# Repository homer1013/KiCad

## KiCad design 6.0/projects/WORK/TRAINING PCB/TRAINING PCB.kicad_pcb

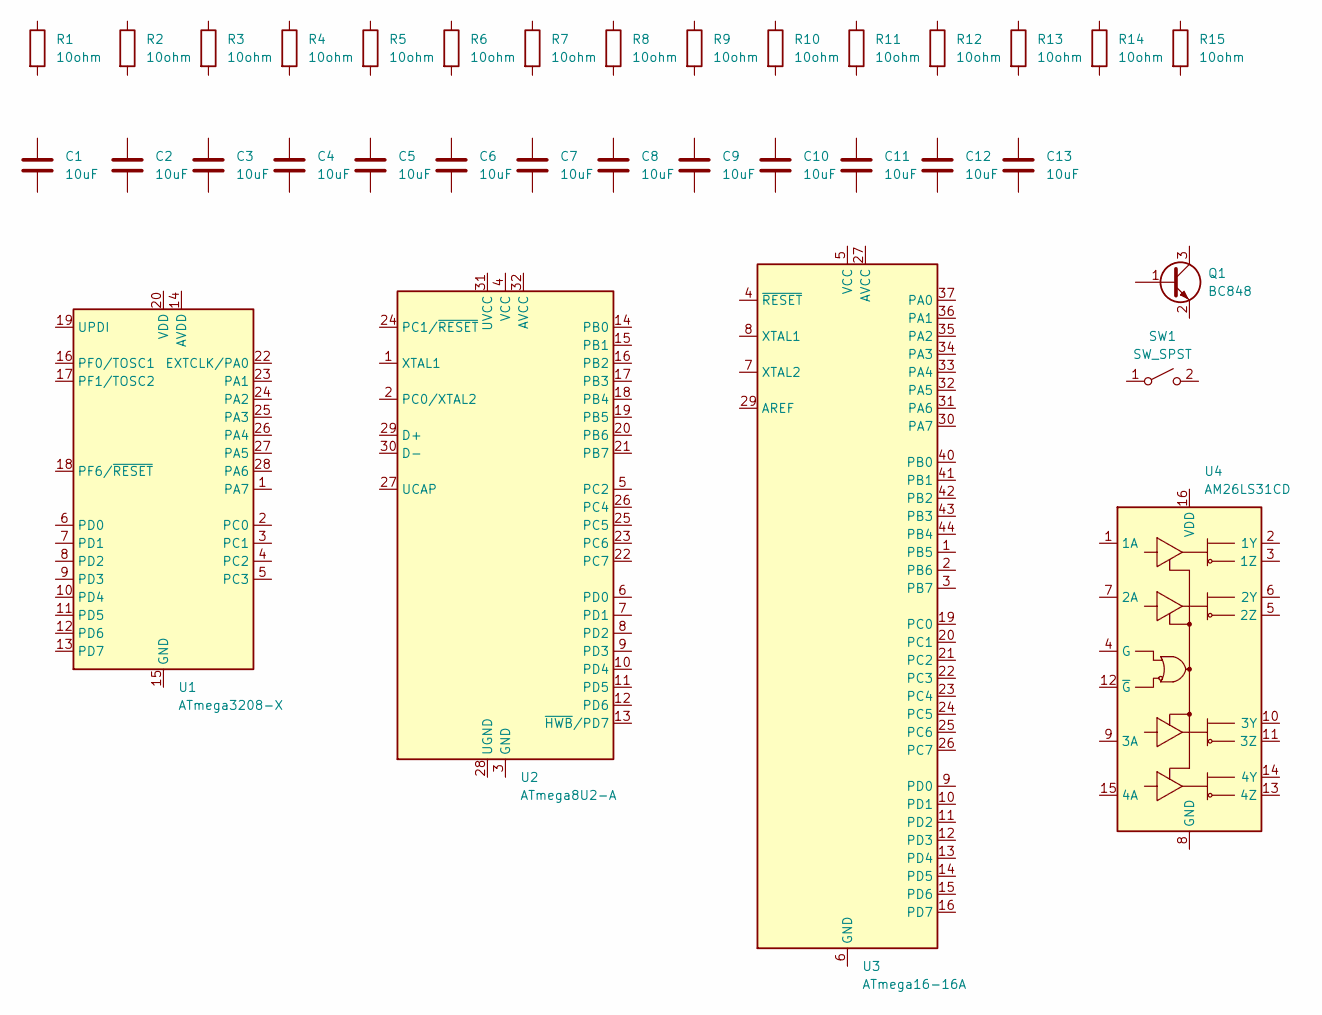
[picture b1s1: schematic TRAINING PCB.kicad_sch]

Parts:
C1: 10uF; C_0201_0603Metric
C2: 10uF; C_0402_1005Metric
C3: 10uF; C_0504_1310Metric
C4: 10uF; C_0603_1608Metric
C5: 10uF; C_0805_2012Metric
C6: 10uF; C_01005_0402Metric
C7: 10uF; C_1206_3216Metric
C8: 10uF; C_1210_3225Metric
C9: 10uF; C_1812_4532Metric
C10: 10uF; C_1825_4564Metric
C11: 10uF; C_2220_5650Metric
C12: 10uF; C_2225_5664Metric
C13: 10uF; C_3640_9110Metric
Q1: BC848; SOT-23
R1: 10ohm; R_0201_0603Metric
R2: 10ohm; R_0402_1005Metric
R3: 10ohm; R_0603_1608Metric
R4: 10ohm; R_0805_2012Metric
R5: 10ohm; R_0815_2038Metric
R6: 10ohm; R_01005_0402Metric
R7: 10ohm; R_1020_2550Metric
R8: 10ohm; R_1206_3216Metric
R9: 10ohm; R_1210_3225Metric
R10: 10ohm; R_1218_3246Metric
R11: 10ohm; R_1812_4532Metric
R12: 10ohm; R_2010_5025Metric
R13: 10ohm; R_2512_6332Metric
R14: 10ohm; R_2816_7142Metric
R15: 10ohm; R_4020_10251Metric
SW1: SW_SPST; SW_SPST_B3SL-1022P
U1: ATmega3208-X; SSOP-28_5.3x10.2mm_P0.65mm
U2: ATmega8U2-A; TQFP-32_7x7mm_P0.8mm
U3: ATmega16-16A; TQFP-44_10x10mm_P0.8mm
U4: AM26LS31CD; SOIC-16_3.9x9.9mm_P1.27mm

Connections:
unnamed: U1.15 (GND), U1.21 (GND)
unnamed: U3.5 (VCC), U3.17 (VCC), U3.38 (VCC)
unnamed: U3.6 (GND), U3.18 (GND), U3.28 (GND), U3.39 (GND)

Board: 2 copper layers, 34 parts (0 on the bottom side), 3 nets, no tracks yet.

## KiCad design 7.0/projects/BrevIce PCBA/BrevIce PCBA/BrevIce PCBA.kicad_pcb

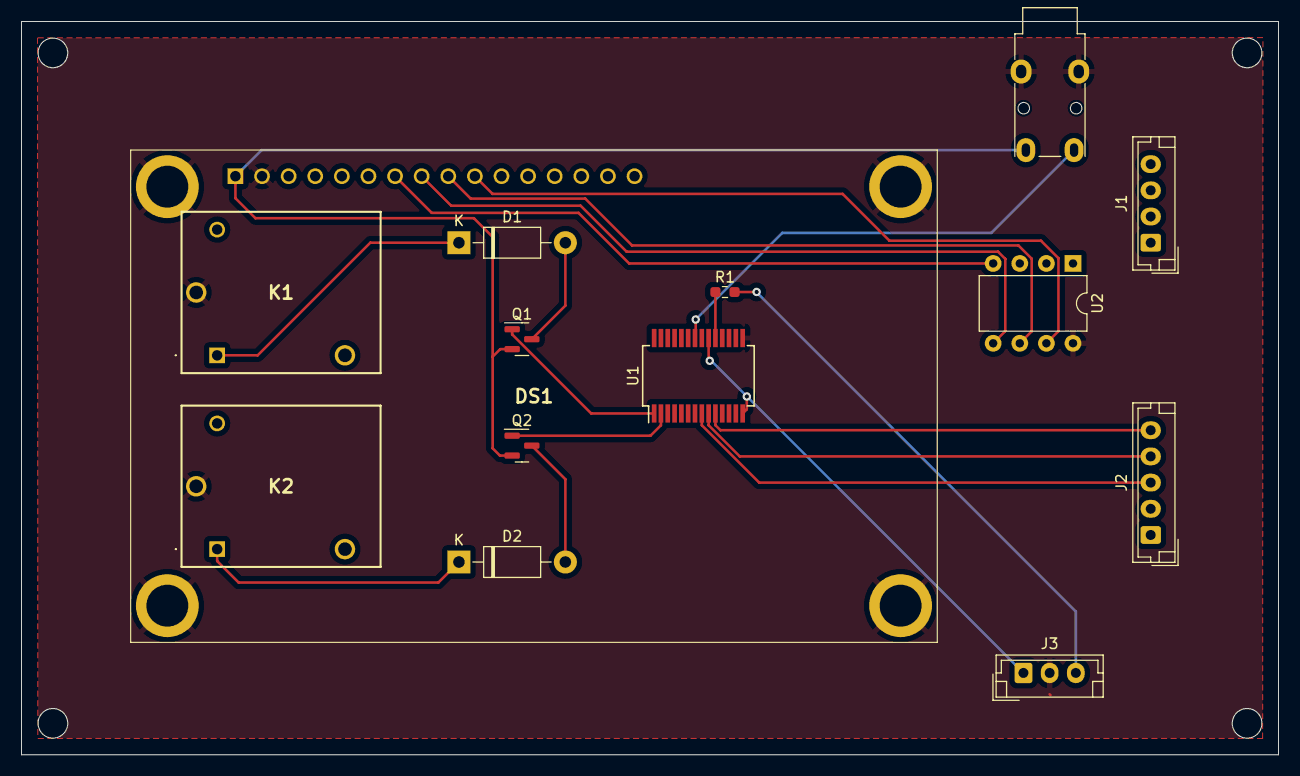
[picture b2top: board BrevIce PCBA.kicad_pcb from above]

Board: 2 copper layers, 120.0 x 70.0 mm, 14 parts (0 on the bottom side), 19 nets.

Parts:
D1, D2: 1N4001; D_DO-41_SOD81_P10.16mm_Horizontal
DS1: NHD-0420AZ-FL-YBW-33V3; NHD0420AZFLYBW33V3
J1: Conn_01x04_Socket; JST_EH_B4B-EH-A_1x04_P2.50mm_Vertical
J2: Conn_01x05_Socket; JST_EH_B5B-EH-A_1x05_P2.50mm_Vertical
J3: Conn_01x03_Socket; JST_EH_B3B-EH-A_1x03_P2.50mm_Vertical
J4: AudioPlug3; Jack_3.5mm_Lumberg_1503_07_Horizontal
K1, K2: AWHSH105D00G
Q1, Q2: AO3400A; SOT-23
R1: 4.7K; R_0603_1608Metric_Pad0.98x0.95mm_HandSolder
U1: ATmega3208-X; SSOP-28_5.3x10.2mm_P0.65mm
U2: PCF8574; DIP-8_W7.62mm

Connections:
+5V: DS1.1 (VSS), J4.S, Q1.2 (S), Q2.2 (S)
GND: DS1.2 (VDD), DS1.MH1, DS1.MH2, DS1.MH3, DS1.MH4, J3.2, J4.T, K1.4 (COM), K2.4 (COM), U1.15 (GND), U1.21 (GND), U2.8 (VSS)
unnamed: D1.2 (A), Q1.3 (D)
unnamed: D1.1 (K), K1.1 (COIL_1)
unnamed: D2.2 (A), Q2.3 (D)
unnamed: D2.1 (K), K2.1 (COIL_1)
unnamed: DS1.7 (DB0), U2.4 (P0)
unnamed: DS1.8 (DB1), U2.5 (P1)
unnamed: DS1.9 (DB2), U2.6 (P2)
unnamed: DS1.10 (DB3), U2.7 (P3)
unnamed: J2.3, U1.8 (PD2)
unnamed: J2.4, U1.9 (PD3)
unnamed: J2.5, U1.10 (PD4)
unnamed: J3.1, U1.14 (AVDD), U1.20 (VDD)
unnamed: J3.3, R1.2
unnamed: Q1.1 (G), U1.1 (PA7)
unnamed: Q2.1 (G), U1.2 (PC0)
unnamed: J4.R, U1.22 (EXTCLK/PA0)
unnamed: R1.1, U1.19 (UPDI)

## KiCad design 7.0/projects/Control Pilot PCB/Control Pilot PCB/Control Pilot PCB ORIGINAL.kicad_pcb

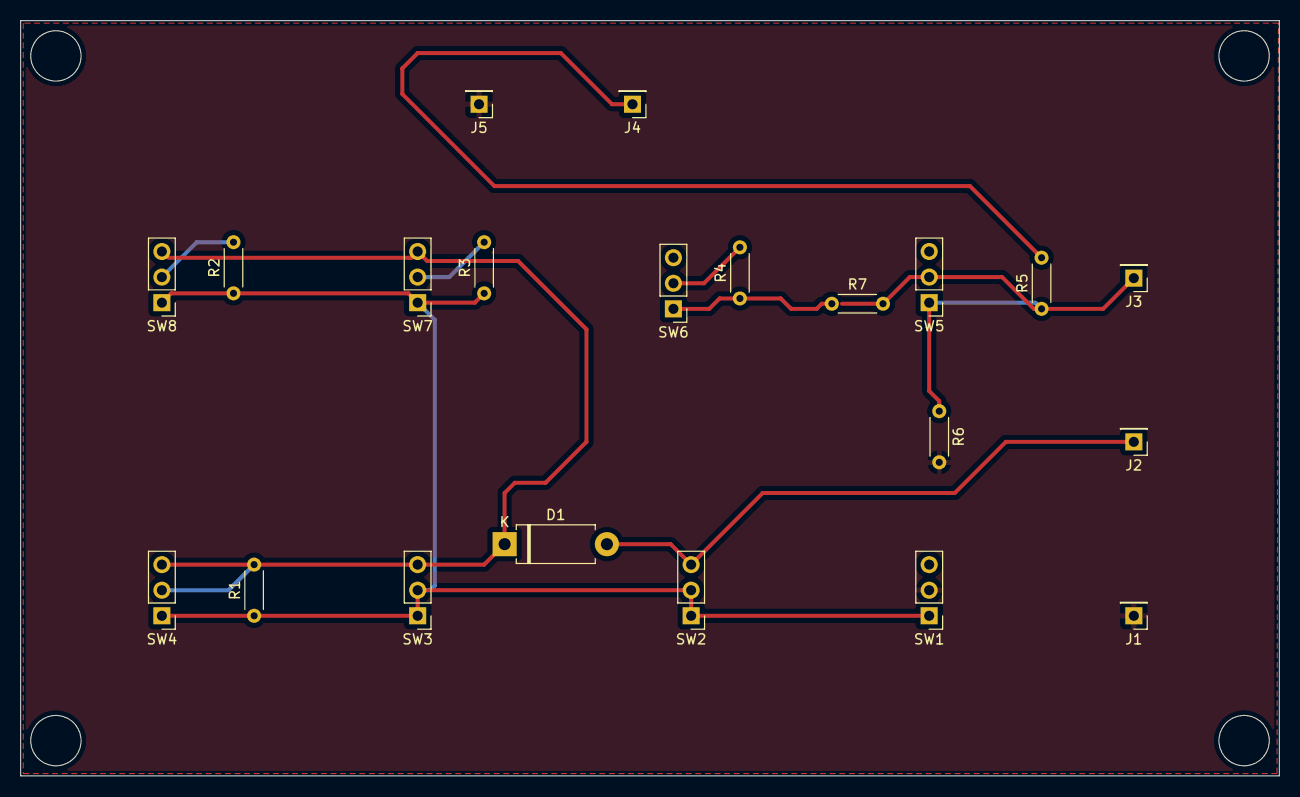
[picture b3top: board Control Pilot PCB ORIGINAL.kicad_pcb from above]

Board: 2 copper layers, 125.0 x 75.0 mm, 21 parts (0 on the bottom side), 11 nets.

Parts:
D1: D; D_DO-15_P10.16mm_Horizontal
J1, J2, J3, J4, J5: Conn_01x01; PinHeader_1x01_P2.54mm_Vertical
R1: 2.74K; R_Axial_DIN0204_L3.6mm_D1.6mm_P5.08mm_Horizontal
R2: 1.3K; R_Axial_DIN0204_L3.6mm_D1.6mm_P5.08mm_Horizontal
R3: 270; R_Axial_DIN0204_L3.6mm_D1.6mm_P5.08mm_Horizontal
R4, R5: 330; R_Axial_DIN0204_L3.6mm_D1.6mm_P5.08mm_Horizontal
R6: 2.7K; R_Axial_DIN0204_L3.6mm_D1.6mm_P5.08mm_Horizontal
R7: 150; R_Axial_DIN0204_L3.6mm_D1.6mm_P5.08mm_Horizontal
SW1, SW2, SW3, SW4, SW5, SW6, SW7, SW8: SW_SPDT; PinHeader_1x03_P2.54mm_Vertical

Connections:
+5V: J4.1, R5.2
Earth_Protective: J1.1, J5.1, R6.2, SW1.2 (B)
unnamed: D1.2 (A), J2.1, SW2.3 (C)
unnamed: D1.1 (K), R1.2, SW3.3 (C), SW4.2 (B), SW4.3 (C), SW7.3 (C), SW8.3 (C)
unnamed: J3.1, R7.2, SW5.2 (B)
unnamed: R1.1, R2.1, R3.1, SW1.1 (A), SW2.1 (A), SW2.2 (B), SW3.1 (A), SW3.2 (B), SW4.1 (A), SW7.1 (A), SW8.1 (A)
unnamed: R5.1, R6.1, SW5.1 (A)
unnamed: R4.1, R7.1, SW6.1 (A)
unnamed: R4.2, SW6.2 (B)
unnamed: R3.2, SW7.2 (B)
unnamed: R2.2, SW8.2 (B)

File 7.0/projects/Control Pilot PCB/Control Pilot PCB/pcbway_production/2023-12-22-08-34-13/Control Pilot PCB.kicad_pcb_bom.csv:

designator,quantity,value,pack,mpn,mount_type
D1,1,D,D_DO-15_P10.16mm_Horizontal,,tht
"J1, J2, J3, J4, J5",5,Conn_01x01,PinHeader_1x01_P2.54mm_Vertical,,tht
R1,1,2.74K,R_Axial_DIN0204_L3.6mm_D1.6mm_P5.08mm_Horizontal,,tht
R2,1,1.3K,R_Axial_DIN0204_L3.6mm_D1.6mm_P5.08mm_Horizontal,,tht
R3,1,270,R_Axial_DIN0204_L3.6mm_D1.6mm_P5.08mm_Horizontal,,tht
"R4, R5",2,330,R_Axial_DIN0204_L3.6mm_D1.6mm_P5.08mm_Horizontal,,tht
R6,1,2.7K,R_Axial_DIN0204_L3.6mm_D1.6mm_P5.08mm_Horizontal,,tht
R7,1,150,R_Axial_DIN0204_L3.6mm_D1.6mm_P5.08mm_Horizontal,,tht
"SW1, SW2, SW3, SW4, SW5, SW6, SW7, SW8",8,SW_SPDT,PinHeader_1x03_P2.54mm_Vertical,,tht

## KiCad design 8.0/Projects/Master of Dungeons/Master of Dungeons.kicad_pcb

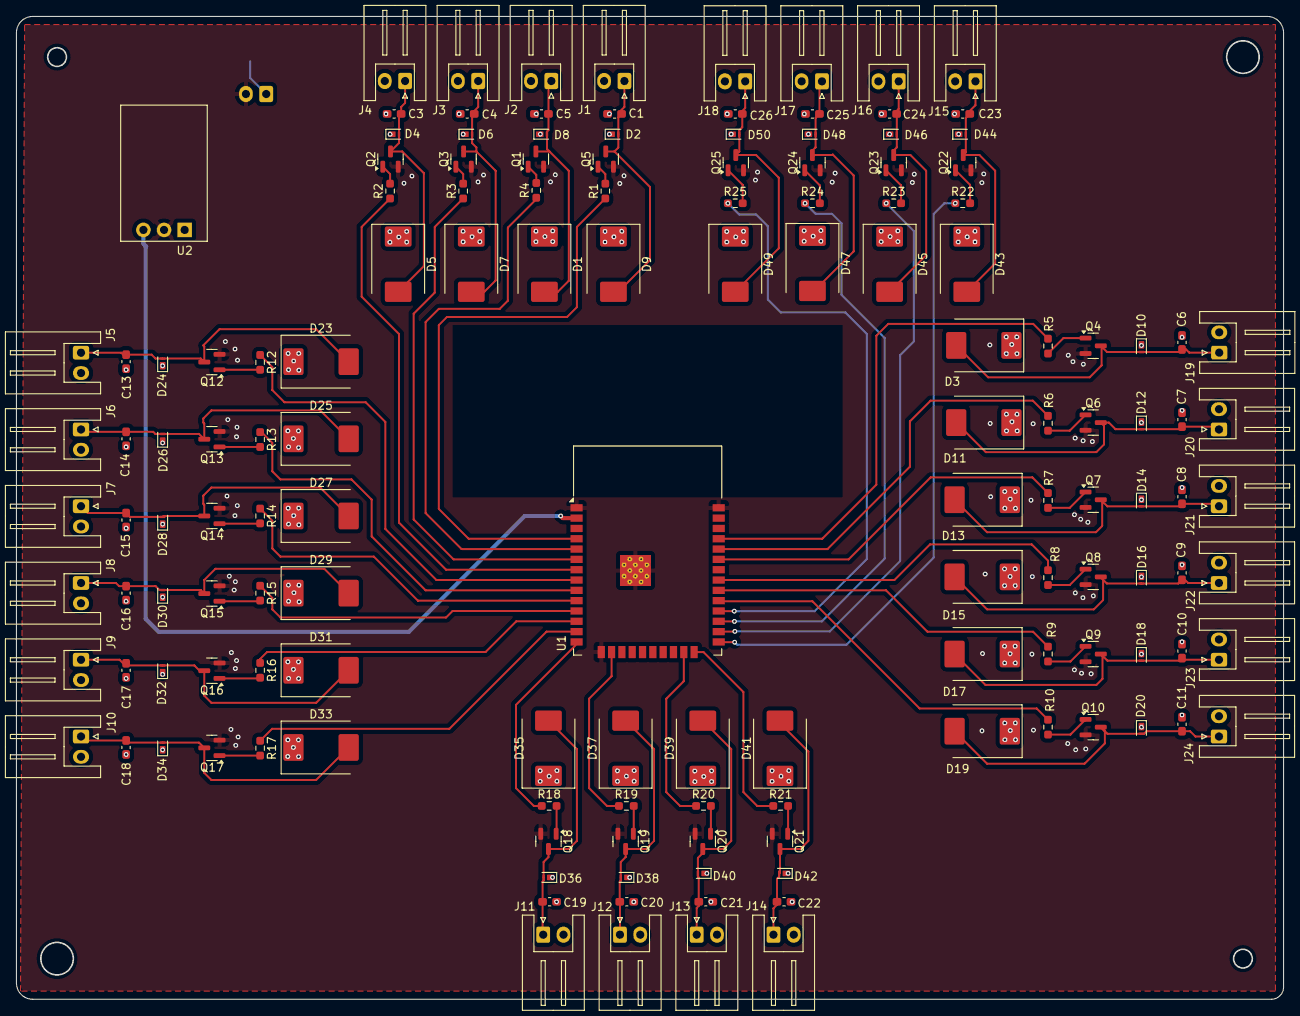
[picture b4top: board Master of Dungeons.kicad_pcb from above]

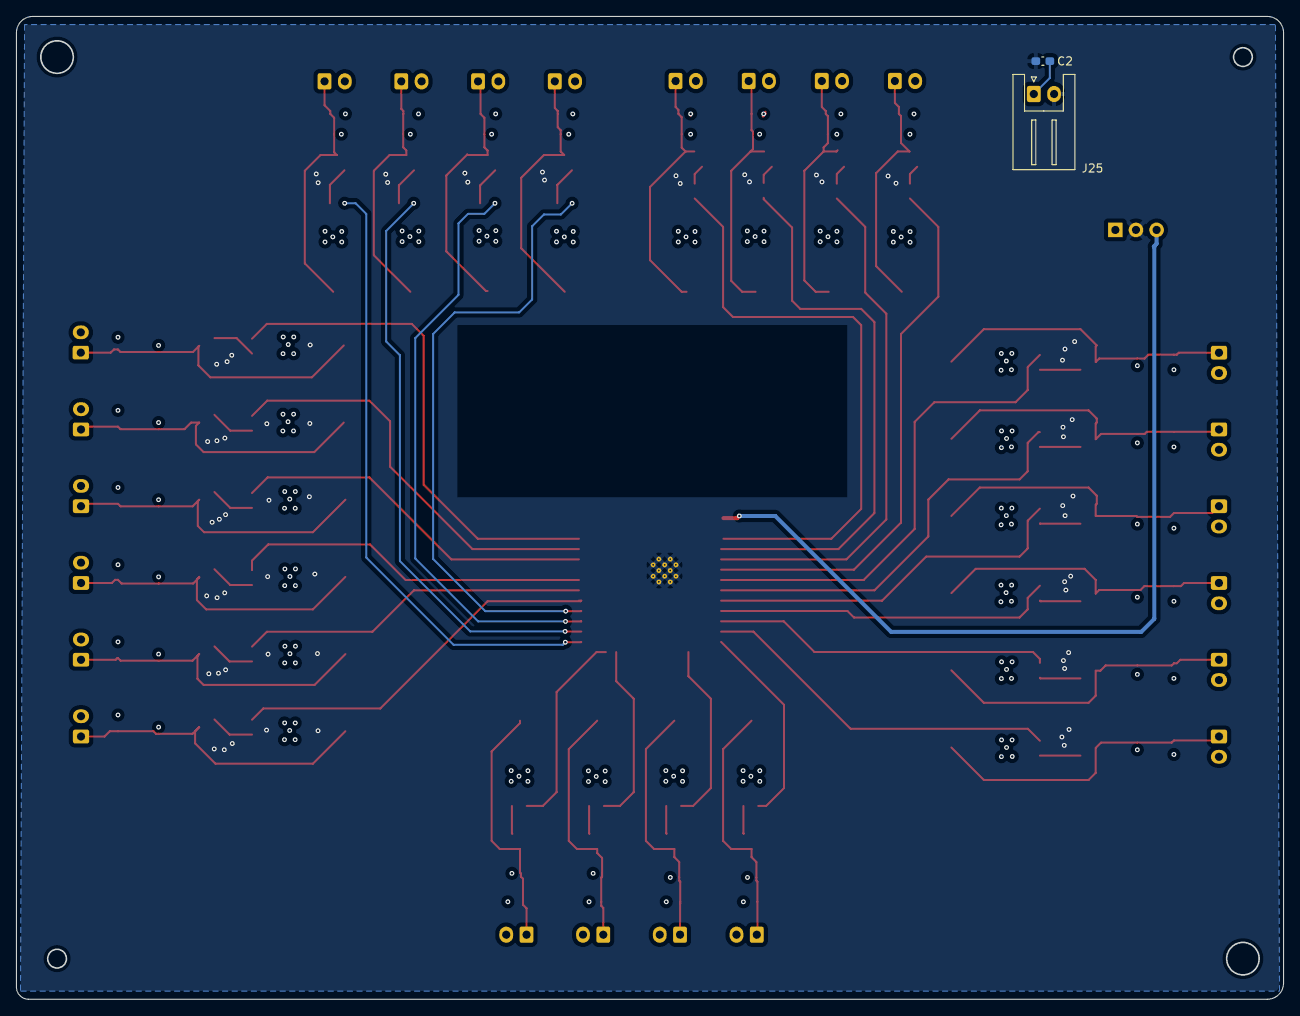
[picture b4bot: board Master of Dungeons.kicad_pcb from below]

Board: 4 copper layers, 156.0 x 121.0 mm, 148 parts (2 on the bottom side), 75 nets.

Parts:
C1, C2, C3, C4, C5, C6, C7, C8, C9, C10, C11, C13, C14, C15, C16, C17, C18, C19, C20, C21, C22, C23, C24, C25, C26: 100nF; C_0603_1608Metric_Pad1.08x0.95mm_HandSolder
D1, D3, D5, D7, D9, D11, D13, D15, D17, D19, D23, D25, D27, D29, D31, D33, D35, D37, D39, D41, D43, D45, D47, D49: B340; D_SMC
D2, D4, D6, D8, D10, D12, D14, D16, D18, D20, D24, D26, D28, D30, D32, D34, D36, D38, D40, D42, D44, D46, D48, D50: PTVS12VZ1USK; Nexperia_DSN1608-2_1.6x0.8mm
J1: sensPin1; JST_XH_S2B-XH-A_1x02_P2.50mm_Horizontal
J2: sensPin2; JST_XH_S2B-XH-A_1x02_P2.50mm_Horizontal
J3: sensPin3; JST_XH_S2B-XH-A_1x02_P2.50mm_Horizontal
J4: sensPin4; JST_XH_S2B-XH-A_1x02_P2.50mm_Horizontal
J5: togglePin1; JST_XH_S2B-XH-A_1x02_P2.50mm_Horizontal
J6: togglePin2; JST_XH_S2B-XH-A_1x02_P2.50mm_Horizontal
J7: togglePin3; JST_XH_S2B-XH-A_1x02_P2.50mm_Horizontal
J8: togglePin4; JST_XH_S2B-XH-A_1x02_P2.50mm_Horizontal
J9: togglePin5; JST_XH_S2B-XH-A_1x02_P2.50mm_Horizontal
J10: togglePin6; JST_XH_S2B-XH-A_1x02_P2.50mm_Horizontal
J11: dimPin1; JST_XH_S2B-XH-A_1x02_P2.50mm_Horizontal
J12: dimPin2; JST_XH_S2B-XH-A_1x02_P2.50mm_Horizontal
J13: dimPin3; JST_XH_S2B-XH-A_1x02_P2.50mm_Horizontal
J14: dimPin4; JST_XH_S2B-XH-A_1x02_P2.50mm_Horizontal
J15: timerPin1; JST_XH_S2B-XH-A_1x02_P2.50mm_Horizontal
J16: timerPin2; JST_XH_S2B-XH-A_1x02_P2.50mm_Horizontal
J17: timerPin3; JST_XH_S2B-XH-A_1x02_P2.50mm_Horizontal
J18: timerPin4; JST_XH_S2B-XH-A_1x02_P2.50mm_Horizontal
J19: sequencePin1; JST_XH_S2B-XH-A_1x02_P2.50mm_Horizontal
J20: sequencePin2; JST_XH_S2B-XH-A_1x02_P2.50mm_Horizontal
J21: sequencePin3; JST_XH_S2B-XH-A_1x02_P2.50mm_Horizontal
J22: sequencePin4; JST_XH_S2B-XH-A_1x02_P2.50mm_Horizontal
J23: sequencePin5; JST_XH_S2B-XH-A_1x02_P2.50mm_Horizontal
J24: sequencePin6; JST_XH_S2B-XH-A_1x02_P2.50mm_Horizontal
J25: 5VDC; JST_XH_S2B-XH-A_1x02_P2.50mm_Horizontal
Q1, Q2, Q3, Q4, Q5, Q6, Q7, Q8, Q9, Q10, Q12, Q13, Q14, Q15, Q16, Q17, Q18, Q19, Q20, Q21, Q22, Q23, Q24, Q25: IRLML6244; SOT-23
R1, R2, R3, R4, R5, R6, R7, R8, R9, R10, R12, R13, R14, R15, R16, R17, R18, R19, R20, R21, R22, R23, R24, R25: 100ohm; R_0603_1608Metric_Pad0.98x0.95mm_HandSolder
U1: ESP32-WROOM-32D
U2: OKI-78SR-3.3_1.5-W36H-C; Converter_DCDC_Murata_OKI-78SR_Horizontal

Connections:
+5V: C1.1, C3.1, C4.1, C5.1, C6.1, C7.1, C8.1, C9.1, C10.1, C11.1, C13.1, C14.1, C15.1, C16.1, C17.1, C18.1, C19.1, C20.1, C21.1, C22.1, C23.1, C24.1, C25.1, C26.1, D1.1 (K), D2.1 (K), D3.1 (K), D4.1 (K), D5.1 (K), D6.1 (K), D7.1 (K), D8.1 (K), D9.1 (K), D10.1 (K), D11.1 (K), D12.1 (K), D13.1 (K), D14.1 (K), D15.1 (K), D16.1 (K), D17.1 (K), D18.1 (K), D19.1 (K), D20.1 (K), D23.1 (K), D24.1 (K), D25.1 (K), D26.1 (K), D27.1 (K), D28.1 (K), D29.1 (K), D30.1 (K), D31.1 (K), D32.1 (K), D33.1 (K), D34.1 (K), D35.1 (K), D36.1 (K), D37.1 (K), D38.1 (K), D39.1 (K), D40.1 (K), D41.1 (K), D42.1 (K), D43.1 (K), D44.1 (K), D45.1 (K), D46.1 (K), D47.1 (K), D48.1 (K), D49.1 (K), D50.1 (K), J1.2, J2.2, J3.2, J4.2, J5.2, J6.2, J7.2, J8.2, J9.2, J10.2, J11.2, J12.2, J13.2, J14.2, J15.2, J16.2, J17.2, J18.2, J19.2, J20.2, J21.2, J22.2, J23.2, J24.2, J25.1, U2.1 (IN)
DIM1: R18.1, U1.14 (IO12)
DIM2: R19.1, U1.16 (IO13)
DIM3: R20.1, U1.23 (IO15)
DIM4: R21.1, U1.24 (IO2)
GND: C2.1, J25.2, Q1.2 (S), Q2.2 (S), Q3.2 (S), Q4.2 (S), Q5.2 (S), Q6.2 (S), Q7.2 (S), Q8.2 (S), Q9.2 (S), Q10.2 (S), Q12.2 (S), Q13.2 (S), Q14.2 (S), Q15.2 (S), Q16.2 (S), Q17.2 (S), Q18.2 (S), Q19.2 (S), Q20.2 (S), Q21.2 (S), Q22.2 (S), Q23.2 (S), Q24.2 (S), Q25.2 (S), U1.1 (GND), U1.15 (GND), U1.38 (GND), U1.39 (GND), U2.2 (GND)
unnamed: C5.2, D1.2 (A), D8.2 (A), J2.1, Q1.3 (D)
unnamed: C1.2, D2.2 (A), D9.2 (A), J1.1, Q5.3 (D)
unnamed: C3.2, D4.2 (A), D5.2 (A), J4.1, Q2.3 (D)
unnamed: C4.2, D6.2 (A), D7.2 (A), J3.1, Q3.3 (D)
unnamed: C6.2, D3.2 (A), D10.2 (A), J19.1, Q4.3 (D)
unnamed: C7.2, D11.2 (A), D12.2 (A), J20.1, Q6.3 (D)
unnamed: C8.2, D13.2 (A), D14.2 (A), J21.1, Q7.3 (D)
unnamed: C9.2, D15.2 (A), D16.2 (A), J22.1, Q8.3 (D)
unnamed: C10.2, D17.2 (A), D18.2 (A), J23.1, Q9.3 (D)
unnamed: C11.2, D19.2 (A), D20.2 (A), J24.1, Q10.3 (D)
unnamed: C13.2, D23.2 (A), D24.2 (A), J5.1, Q12.3 (D)
unnamed: C14.2, D25.2 (A), D26.2 (A), J6.1, Q13.3 (D)
unnamed: C15.2, D27.2 (A), D28.2 (A), J7.1, Q14.3 (D)
unnamed: C16.2, D29.2 (A), D30.2 (A), J8.1, Q15.3 (D)
unnamed: C17.2, D31.2 (A), D32.2 (A), J9.1, Q16.3 (D)
unnamed: C18.2, D33.2 (A), D34.2 (A), J10.1, Q17.3 (D)
unnamed: C19.2, D35.2 (A), D36.2 (A), J11.1, Q18.3 (D)
unnamed: C20.2, D37.2 (A), D38.2 (A), J12.1, Q19.3 (D)
unnamed: C21.2, D39.2 (A), D40.2 (A), J13.1, Q20.3 (D)
unnamed: C22.2, D41.2 (A), D42.2 (A), J14.1, Q21.3 (D)
unnamed: C23.2, D43.2 (A), D44.2 (A), J15.1, Q22.3 (D)
unnamed: C24.2, D45.2 (A), D46.2 (A), J16.1, Q23.3 (D)
unnamed: C25.2, D47.2 (A), D48.2 (A), J17.1, Q24.3 (D)
unnamed: C26.2, D49.2 (A), D50.2 (A), J18.1, Q25.3 (D)
unnamed: Q1.1 (G), R4.2
unnamed: Q2.1 (G), R2.2
unnamed: Q3.1 (G), R3.2
unnamed: Q4.1 (G), R5.2
unnamed: Q5.1 (G), R1.2
unnamed: Q6.1 (G), R6.2
unnamed: Q7.1 (G), R7.2
unnamed: Q8.1 (G), R8.2
unnamed: Q9.1 (G), R9.2
unnamed: Q10.1 (G), R10.2
unnamed: Q12.1 (G), R12.2
unnamed: Q13.1 (G), R13.2
unnamed: Q14.1 (G), R14.2
unnamed: Q15.1 (G), R15.2
unnamed: Q16.1 (G), R16.2
unnamed: Q17.1 (G), R17.2
unnamed: Q18.1 (G), R18.2
unnamed: Q19.1 (G), R19.2
unnamed: Q20.1 (G), R20.2
unnamed: Q21.1 (G), R21.2
unnamed: Q22.1 (G), R22.2
unnamed: Q23.1 (G), R23.2
unnamed: Q24.1 (G), R24.2
unnamed: Q25.1 (G), R25.2
unnamed: R3.1, U1.6 (IO34)
unnamed: R2.1, U1.7 (IO35)
unnamed: R4.1, U1.5 (SENSOR_VN)
unnamed: R1.1, U1.4 (SENSOR_VP)
unnamed: U1.2 (VDD), U2.3 (OUT)
SEQ1: R5.1, U1.35 (TXD0/IO1)
SEQ2: R6.1, U1.34 (RXD0/IO3)
SEQ3: R7.1, U1.33 (IO21)
SEQ4: R8.1, U1.31 (IO19)
SEQ5: R9.1, U1.30 (IO18)
SEQ6: R10.1, U1.29 (IO5)
TIMER1: R22.1, U1.25 (IO0)
TIMER2: R23.1, U1.26 (IO4)
TIMER3: R24.1, U1.27 (IO16)
TIMER4: R25.1, U1.28 (IO17)
TOG1: R12.1, U1.8 (IO32)
TOG2: R13.1, U1.9 (IO33)
TOG3: R14.1, U1.10 (IO25)
TOG4: R15.1, U1.11 (IO26)
TOG5: R16.1, U1.12 (IO27)
TOG6: R17.1, U1.13 (IO14)

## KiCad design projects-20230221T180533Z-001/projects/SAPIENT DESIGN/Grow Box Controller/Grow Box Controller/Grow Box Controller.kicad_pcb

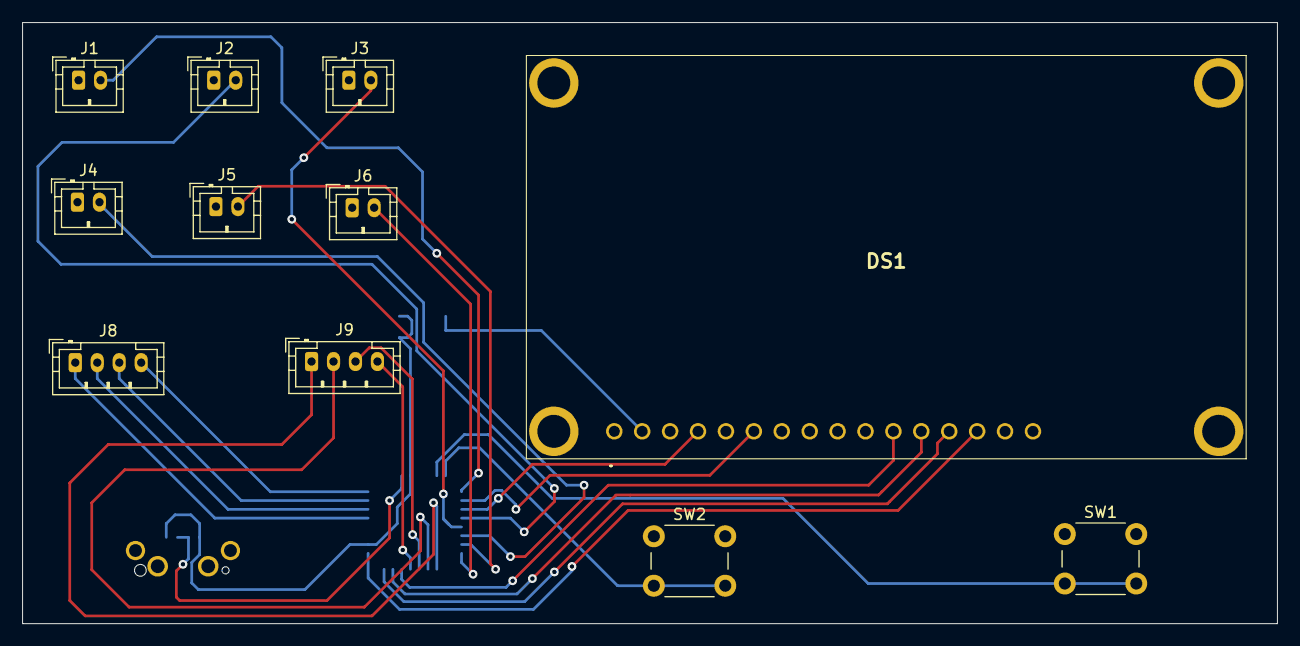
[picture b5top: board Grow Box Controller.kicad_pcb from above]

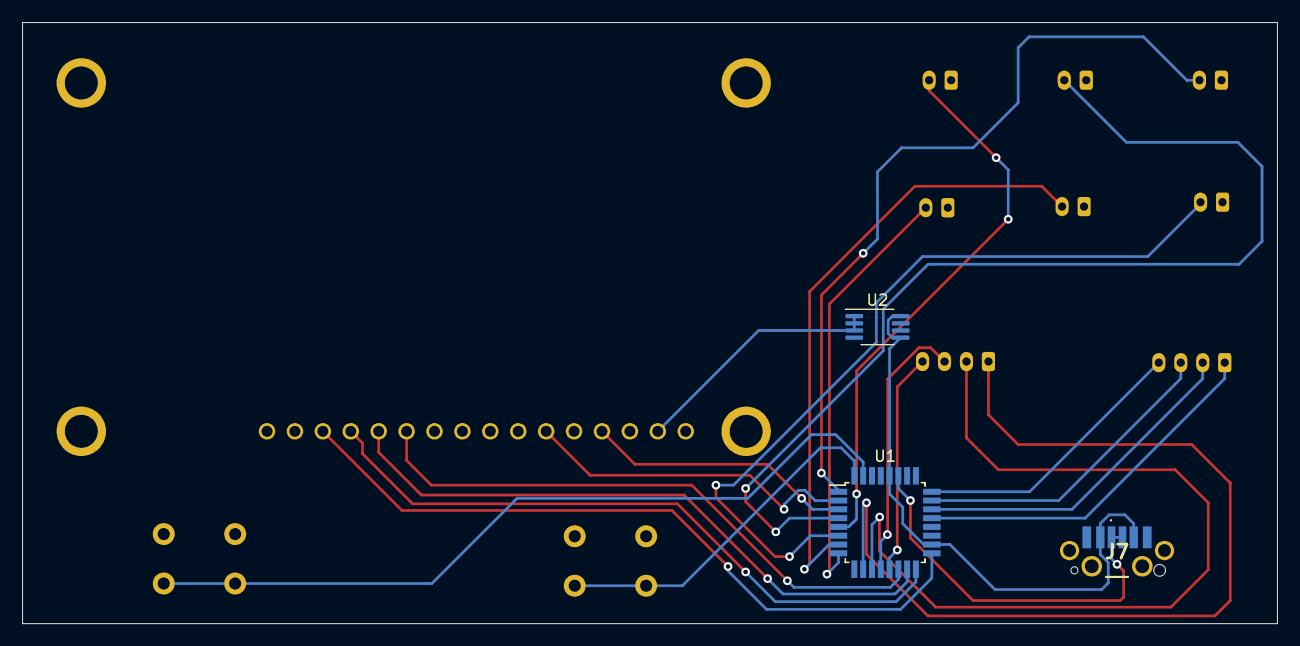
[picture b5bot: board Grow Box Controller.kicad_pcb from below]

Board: 2 copper layers, 114.2 x 54.7 mm, 14 parts (3 on the bottom side), 26 nets.

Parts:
DS1: NHD-0216HZ-FSW-FBW-33V3C; NHD0216HZFSWFBW33V3C
J1: FAN1; JST_PH_B2B-PH-K_1x02_P2.00mm_Vertical
J2: NIT; JST_PH_B2B-PH-K_1x02_P2.00mm_Vertical
J3: POT; JST_PH_B2B-PH-K_1x02_P2.00mm_Vertical
J4: PHO; JST_PH_B2B-PH-K_1x02_P2.00mm_Vertical
J5: ARRAY1; JST_PH_B2B-PH-K_1x02_P2.00mm_Vertical
J6: ARRAY2; JST_PH_B2B-PH-K_1x02_P2.00mm_Vertical
J7: USB4140-GF-0070-C; USB4140GF0070C
J8: MOIST SENS; JST_PH_B4B-PH-K_1x04_P2.00mm_Vertical
J9: NUTR SENS; JST_PH_B4B-PH-K_1x04_P2.00mm_Vertical
SW1, SW2: SW_Push; SW_PUSH_6mm
U1: ATmega3208-A; TQFP-32_7x7mm_P0.8mm
U2: LT1762-3.3; MSOP-8_3x3mm_P0.65mm

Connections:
GND: DS1.1 (VSS), DS1.5 (R/W), DS1.16 (LED-), J7.A12 (GND_1), J7.B12 (GND_2), U1.19 (GND), U1.29 (GND), U2.4 (GND)
unnamed: DS1.4 (RS), U1.3 (PA5)
unnamed: DS1.6 (E), U1.2 (PA4)
unnamed: DS1.11 (DB4), U1.14 (PD4)
unnamed: DS1.12 (DB5), U1.15 (PD5)
unnamed: DS1.13 (DB6), U1.16 (PD6)
unnamed: DS1.14 (DB7), U1.17 (PD7)
unnamed: DS1.2 (VDD), DS1.15 (LED+), U2.1 (OUT), U2.2 (SENSE), U2.3 (BYP)
unnamed: J1.2, U1.1 (PA3)
unnamed: J2.2, U1.4 (PA6)
unnamed: J3.2, U1.5 (PA7)
unnamed: J4.2, U1.6 (PC0)
unnamed: J5.2, U1.7 (PC1)
unnamed: J6.2, U1.8 (PC2)
unnamed: J7.A5 (CC1), J7.B5 (CC2), U1.27 (UPDI)
unnamed: J7.A9 (VBUS_1), J7.B9 (VBUS_2), U1.18 (AVDD), U1.28 (VDD), U2.5 (~SHDN), U2.8 (IN)
unnamed: J8.1, U1.21 (PF1/TOSC2)
unnamed: J8.2, U1.22 (PF2)
unnamed: J8.3, U1.23 (PF3)
unnamed: J8.4, U1.24 (PF4)
unnamed: J9.1, U1.10 (PD0)
unnamed: J9.2, U1.11 (PD1)
unnamed: J9.3, U1.12 (PD2)
unnamed: J9.4, U1.13 (PD3)
unnamed: SW1.2, U1.31 (PA1)
unnamed: SW2.2, U1.32 (PA2)

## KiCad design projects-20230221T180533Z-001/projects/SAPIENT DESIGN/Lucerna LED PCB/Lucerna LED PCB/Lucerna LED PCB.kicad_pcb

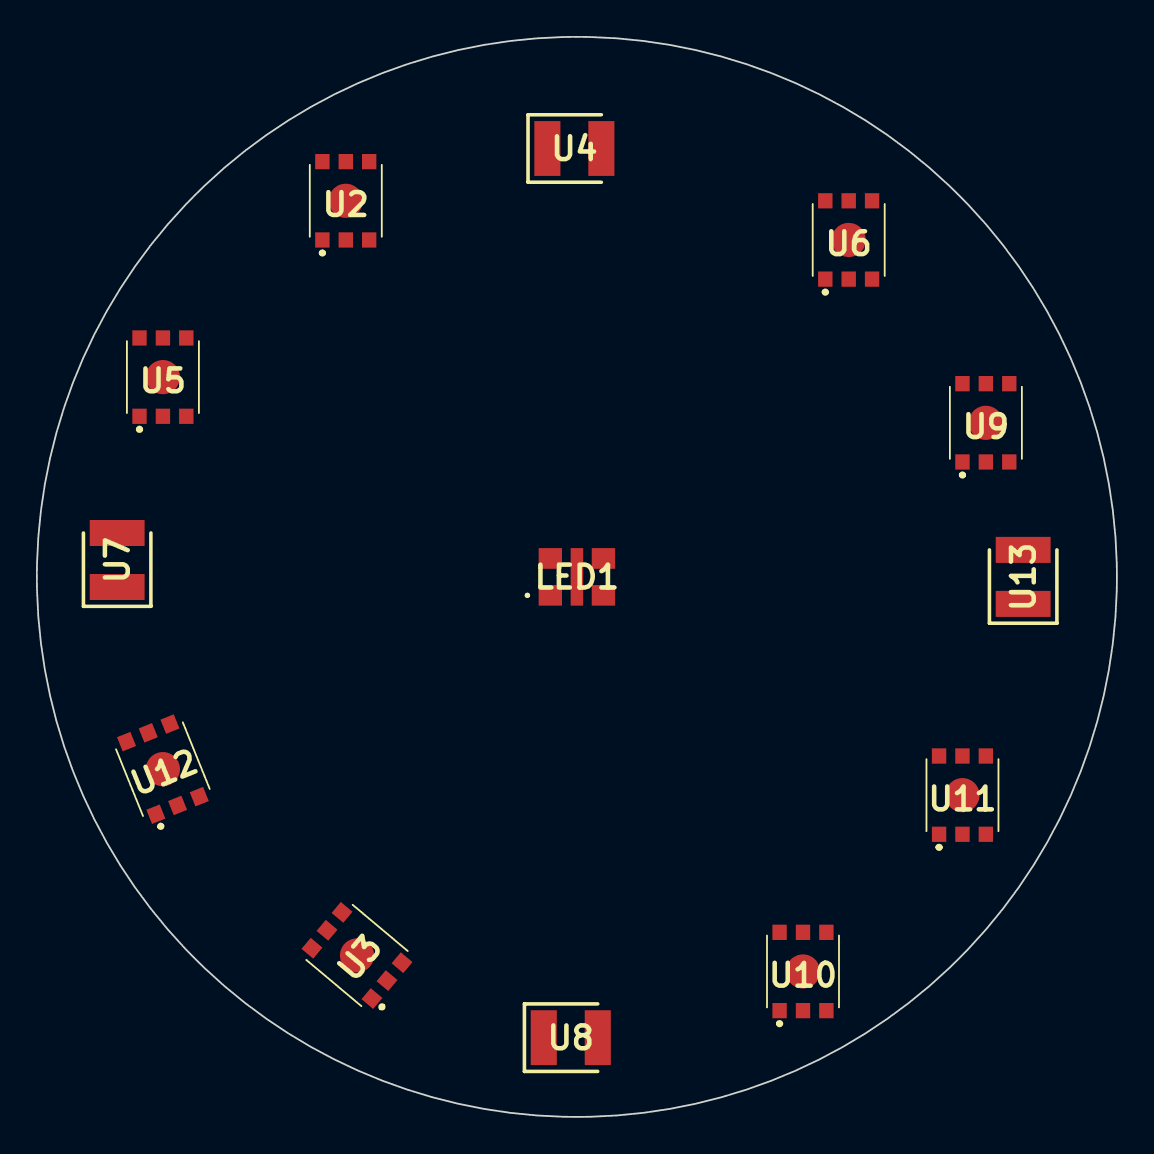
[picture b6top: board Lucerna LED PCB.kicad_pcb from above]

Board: 2 copper layers, 60.0 x 60.0 mm, 14 parts (1 on the bottom side), 20 nets, no tracks yet.

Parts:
LED1: MLBAWT-A1-0000-000W51; MLBAWTA10000000W51
U1: ATmega3208-X; SSOP-28_5.3x10.2mm_P0.65mm
U2, U3, U5, U6, U9, U10, U11, U12: ASMG-PT00-00001; ASMGPT0000001
U4, U7, U8, U13: VLMU3100-GS08; LEDC3228X190M

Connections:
/LED Array/Blue A: U1.6 (PD0), U2.3 (BLUE_A), U5.3 (BLUE_A), U9.3 (BLUE_A), U12.3 (BLUE_A)
/LED Array/Green A: U1.7 (PD1), U2.2 (GREEN_A), U5.2 (GREEN_A), U9.2 (GREEN_A), U12.2 (GREEN_A)
/LED Array/Red A: U1.8 (PD2), U2.1 (RED_A), U5.1 (RED_A), U9.1 (RED_A), U12.1 (RED_A)
/LED Array/UV A: U1.10 (PD4), U4.2 (A), U13.2 (A)
/LED Array/White A: LED1.1 (A_1), LED1.4 (A_2), U1.9 (PD3)
GND: LED1.2 (K_1), LED1.3 (K_2), LED1.5 (EP), U1.15 (GND), U1.21 (GND), U2.7 (THERMAL_PAD), U3.4 (BLUE_K), U3.5 (GREEN_K), U3.6 (RED_K), U3.7 (THERMAL_PAD), U5.7 (THERMAL_PAD), U6.5 (GREEN_K), U6.6 (RED_K), U6.7 (THERMAL_PAD), U7.1 (K), U8.1 (K), U10.4 (BLUE_K), U10.5 (GREEN_K), U10.6 (RED_K), U10.7 (THERMAL_PAD), U11.4 (BLUE_K), U11.5 (GREEN_K), U11.6 (RED_K), U11.7 (THERMAL_PAD)
unnamed: U2.4 (BLUE_K), U6.4 (BLUE_K)
unnamed: U2.5 (GREEN_K), U6.2 (GREEN_A)
unnamed: U2.6 (RED_K), U6.1 (RED_A)
unnamed: U3.1 (RED_A), U5.6 (RED_K)
unnamed: U3.2 (GREEN_A), U5.5 (GREEN_K)
unnamed: U3.3 (BLUE_A), U5.4 (BLUE_K)
unnamed: U4.1 (K), U7.2 (A)
unnamed: U9.4 (BLUE_K), U11.3 (BLUE_A)
unnamed: U9.5 (GREEN_K), U11.2 (GREEN_A)
unnamed: U9.6 (RED_K), U11.1 (RED_A)
unnamed: U10.1 (RED_A), U12.6 (RED_K)
unnamed: U10.2 (GREEN_A), U12.5 (GREEN_K)
unnamed: U10.3 (BLUE_A), U12.4 (BLUE_K)
unnamed: U8.2 (A), U13.1 (K)

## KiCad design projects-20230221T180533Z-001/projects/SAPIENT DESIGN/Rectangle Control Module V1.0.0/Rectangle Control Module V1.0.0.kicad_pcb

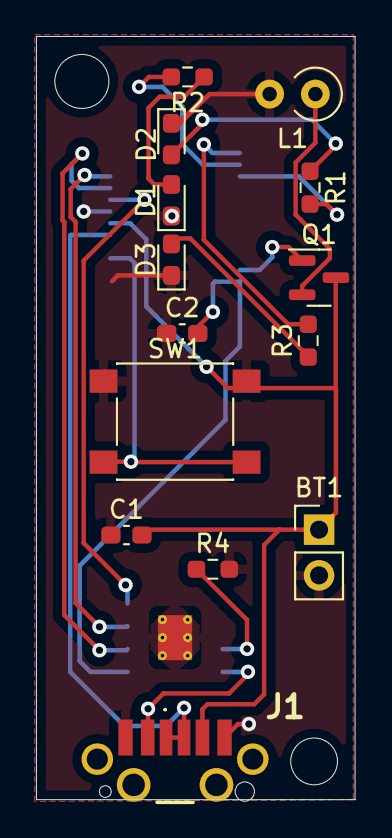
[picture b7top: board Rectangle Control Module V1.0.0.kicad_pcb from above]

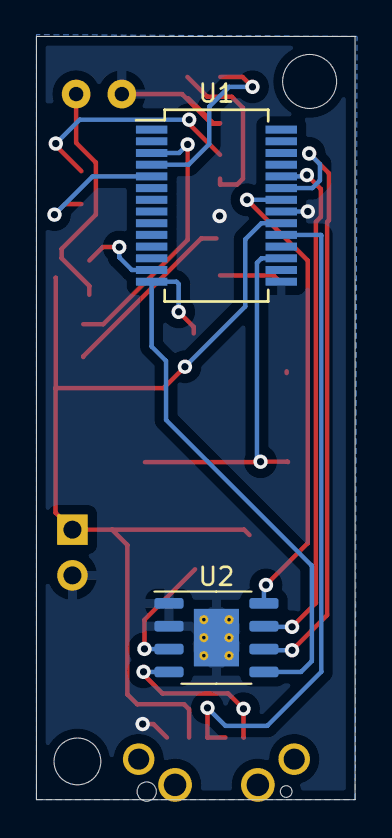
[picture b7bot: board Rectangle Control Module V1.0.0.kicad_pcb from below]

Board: 2 copper layers, 17.7 x 42.4 mm, 16 parts (2 on the bottom side), 18 nets.

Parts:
BT1: Battery_Cell; PinHeader_1x02_P2.54mm_Vertical
C1, C2: 10uF; C_0603_1608Metric_Pad1.08x0.95mm_HandSolder
D1, D2, D3: LED; LED_0603_1608Metric_Pad1.05x0.95mm_HandSolder
J1: USB4140-GF-0070-C; USB4140GF0070C
L1: 2 Ohm; L_Axial_L6.6mm_D2.7mm_P2.54mm_Vertical_Vishay_IM-2
Q1: N-FET; SOT-23
R1, R2, R3: 1 Kohm; R_0603_1608Metric_Pad0.98x0.95mm_HandSolder
R4: 2.8Kohm; R_0603_1608Metric_Pad0.98x0.95mm_HandSolder
SW1: btn; SW_Push_1P1T_NO_6x6mm_H9.5mm
U1: ATmega3208-X; SSOP-28_5.3x10.2mm_P0.65mm
U2: TP4056; SOIC-8-1EP_3.9x4.9mm_P1.27mm_EP2.514x3.2mm_ThermalVias

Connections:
GND: BT1.2 (-), C1.1, C2.1, D1.1 (K), D2.1 (K), D3.1 (K), J1.A12 (GND_1), J1.B12 (GND_2), L1.2, R4.2, SW1.1, U1.15 (GND), U1.21 (GND), U2.1 (TEMP1), U2.2 (PROG2), U2.9 (EP)
unnamed: BT1.1 (+), C1.2, J1.A9 (VBUS_1), Q1.3 (D), U1.20 (VDD)
unnamed: C2.2, U1.14 (AVDD), U2.5 (BAT)
unnamed: D1.2 (A), R2.1
unnamed: D2.2 (A), R1.1
unnamed: D3.2 (A), R3.1
unnamed: J1.A5 (CC1), J1.B5 (CC2), U1.19 (UPDI)
unnamed: J1.B9 (VBUS_2), U2.4 (VCC4)
unnamed: L1.1, Q1.2 (S)
unnamed: Q1.1 (G), U1.13 (PD7)
unnamed: R1.2, U1.5 (PC3)
unnamed: R2.2, U1.4 (PC2)
unnamed: R3.2, U1.3 (PC1)
unnamed: R4.1, U2.3 (GND_3)
unnamed: SW1.2, U1.17 (PF1/TOSC2)
unnamed: U1.22 (EXTCLK/PA0), U2.8 (CE)
unnamed: U1.23 (PA1), U2.6 (~STDBY)
unnamed: U1.24 (PA2), U2.7 (~CHRG)

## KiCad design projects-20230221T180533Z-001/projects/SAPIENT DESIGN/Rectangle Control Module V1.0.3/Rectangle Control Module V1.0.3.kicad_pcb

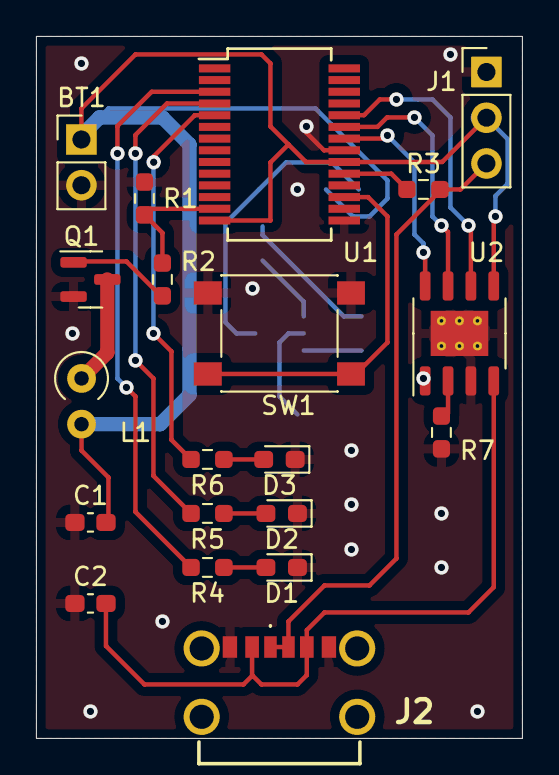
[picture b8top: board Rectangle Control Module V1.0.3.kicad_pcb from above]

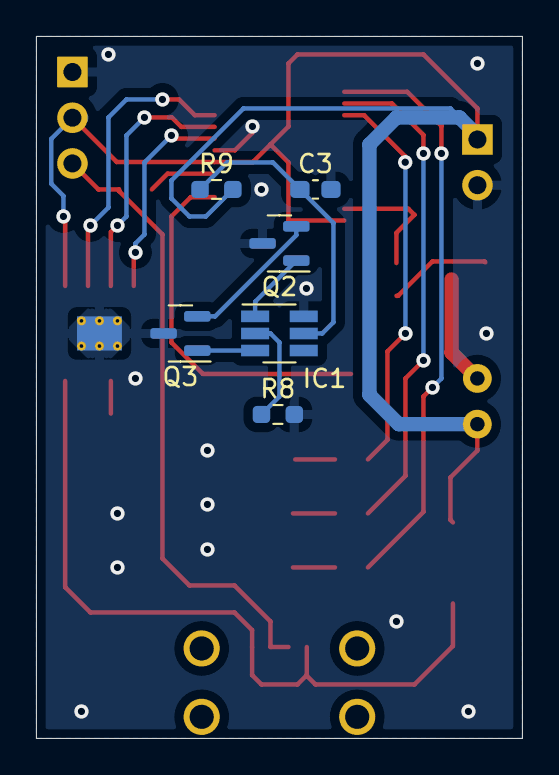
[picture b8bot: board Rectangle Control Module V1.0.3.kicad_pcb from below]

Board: 2 copper layers, 27.0 x 39.0 mm, 26 parts (6 on the bottom side), 24 nets.

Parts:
BT1: Battery_Cell; PinHeader_1x02_P2.54mm_Vertical
C1, C2: 10uF; C_0603_1608Metric_Pad1.08x0.95mm_HandSolder
C3: .1uF; C_0603_1608Metric_Pad1.08x0.95mm_HandSolder
D1, D2, D3: LED; LED_0603_1608Metric_Pad1.05x0.95mm_HandSolder
IC1: DW01A-G; SOT-23-6_Handsoldering
J1: Conn_01x03_Male; PinHeader_1x03_P2.54mm_Vertical
J2: USB4140-GF-0070-C; USB4125GFA0190
L1: 2 Ohm; L_Axial_L6.6mm_D2.7mm_P2.54mm_Vertical_Vishay_IM-2
Q1, Q2, Q3: AO3400A; SOT-23
R1: 100K; R_0603_1608Metric_Pad0.98x0.95mm_HandSolder
R2, R3: 4.7K; R_0603_1608Metric_Pad0.98x0.95mm_HandSolder
R4, R5, R6: 1K; R_0603_1608Metric_Pad0.98x0.95mm_HandSolder
R7: 2.8K; R_0603_1608Metric_Pad0.98x0.95mm_HandSolder
R8: 2K; R_0603_1608Metric_Pad0.98x0.95mm_HandSolder
R9: 330; R_0603_1608Metric_Pad0.98x0.95mm_HandSolder
SW1: btn; SW_Push_1P1T_NO_6x6mm_H9.5mm
U1: ATmega3208-X; SSOP-28_5.3x10.2mm_P0.65mm
U2: TP4056; SOIC-8-1EP_3.9x4.9mm_P1.27mm_EP2.514x3.2mm_ThermalVias

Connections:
GND: BT1.2 (-), C1.1, C2.1, C3.2, D1.1 (K), D2.1 (K), D3.1 (K), IC1.6 (GND), J1.1, J2.A12 (GND_1), J2.B12 (GND_2), Q1.2, Q2.3, Q3.3, R1.1, R7.2, R8.2, SW1.1, U1.15 (GND), U1.21 (GND), U2.1 (TEMP1), U2.3 (GND_3), U2.9 (EP)
unnamed: BT1.1 (+), C1.2, J1.2, L1.2, R9.2, U1.14 (AVDD), U1.20 (VDD), U2.5 (BAT)
unnamed: C2.2, J2.A9 (VBUS_1), J2.B9 (VBUS_2), U2.4 (VCC4)
unnamed: C3.1, IC1.5 (VCC), R9.1
unnamed: D1.2 (A), R4.1
unnamed: D2.2 (A), R5.1
unnamed: D3.2 (A), R6.1
unnamed: IC1.1 (OD), Q2.1
unnamed: IC1.2 (CS), R8.1
unnamed: IC1.3 (OC), Q3.1
unnamed: J1.3, J2.A5 (CC1), J2.B5 (CC2), R3.2
unnamed: L1.1, Q1.3
unnamed: Q1.1, R2.1
unnamed: Q2.2, Q3.2
unnamed: R1.2, R2.2, U1.13 (PD7)
unnamed: R3.1, U1.19 (UPDI)
unnamed: R4.2, U1.3 (PC1)
unnamed: R5.2, U1.4 (PC2)
unnamed: R6.2, U1.5 (PC3)
unnamed: R7.1, U2.2 (PROG2)
unnamed: SW1.2, U1.17 (PF1/TOSC2)
unnamed: U1.22 (EXTCLK/PA0), U2.8 (CE)
unnamed: U1.23 (PA1), U2.7 (~CHRG)
unnamed: U1.24 (PA2), U2.6 (~STDBY)
